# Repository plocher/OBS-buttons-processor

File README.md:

# OBS-buttons
## License: CERN Open Hardware Licence v1.2

Processor Board for Arduino Keyboard Box

An Arduino Pro-mini and connectors for IO daughterboard

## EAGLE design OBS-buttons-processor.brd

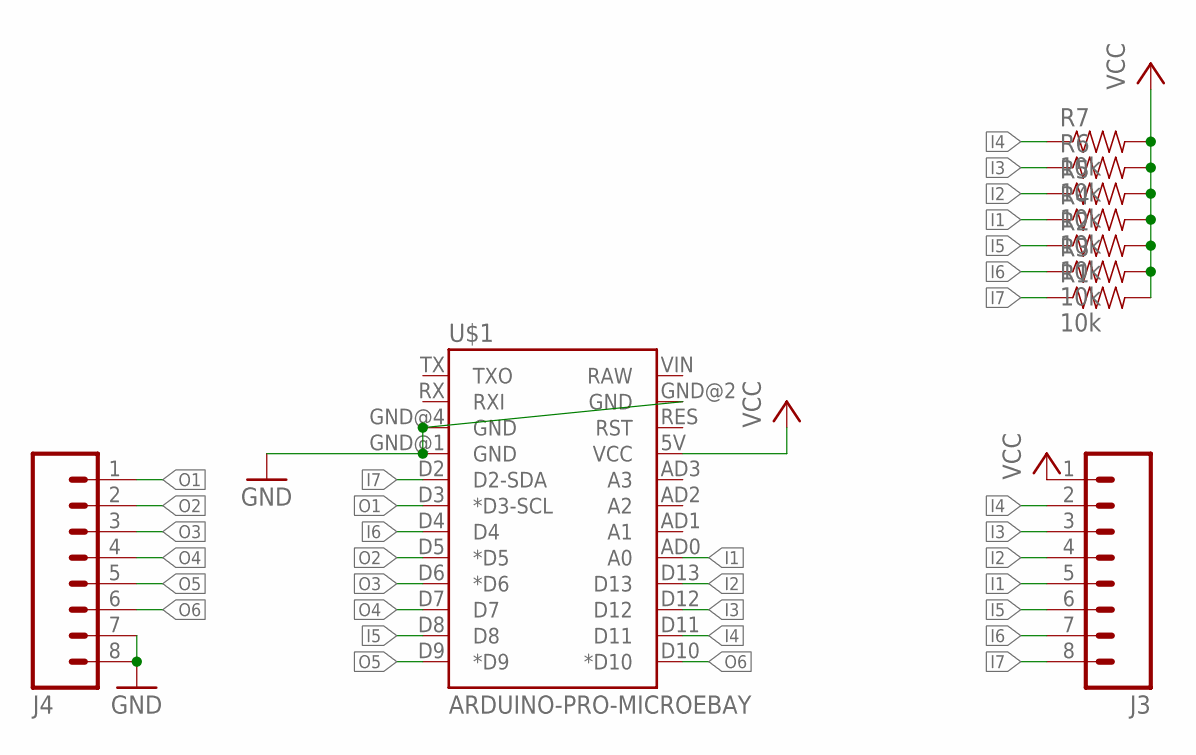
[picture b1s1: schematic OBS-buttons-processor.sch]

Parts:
J3, J4: CONNECTOR-M08LOCK; 1X08_LOCK
R1, R2, R3, R4, R5, R6, R7: 10k; AXIAL-0.4-RES
U$1: ARDUINO-PRO-MICROEBAY; ARDUINO-PRO-MICRO

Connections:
GND: J4.7, J4.8, U$1.GND@1 (GND), U$1.GND@2 (GND), U$1.GND@4 (GND)
I1: J3.5, R4.P$1 (1), U$1.AD0 (A0)
I2: J3.4, R5.P$1 (1), U$1.D13
I3: J3.3, R6.P$1 (1), U$1.D12
I4: J3.2, R7.P$1 (1), U$1.D11
I5: J3.6, R2.P$1 (1), U$1.D8
I6: J3.7, R3.P$1 (1), U$1.D4
I7: J3.8, R1.P$1 (1), U$1.D2 (D2-SDA)
O1: J4.1, U$1.D3 (*D3-SCL)
O2: J4.2, U$1.D5 (*D5)
O3: J4.3, U$1.D6 (*D6)
O4: J4.4, U$1.D7
O5: J4.5, U$1.D9 (*D9)
O6: J4.6, U$1.D10 (*D10)
VCC: J3.1, R1.P$2 (2), R2.P$2 (2), R3.P$2 (2), R4.P$2 (2), R5.P$2 (2), R6.P$2 (2), R7.P$2 (2), U$1.5V (VCC)

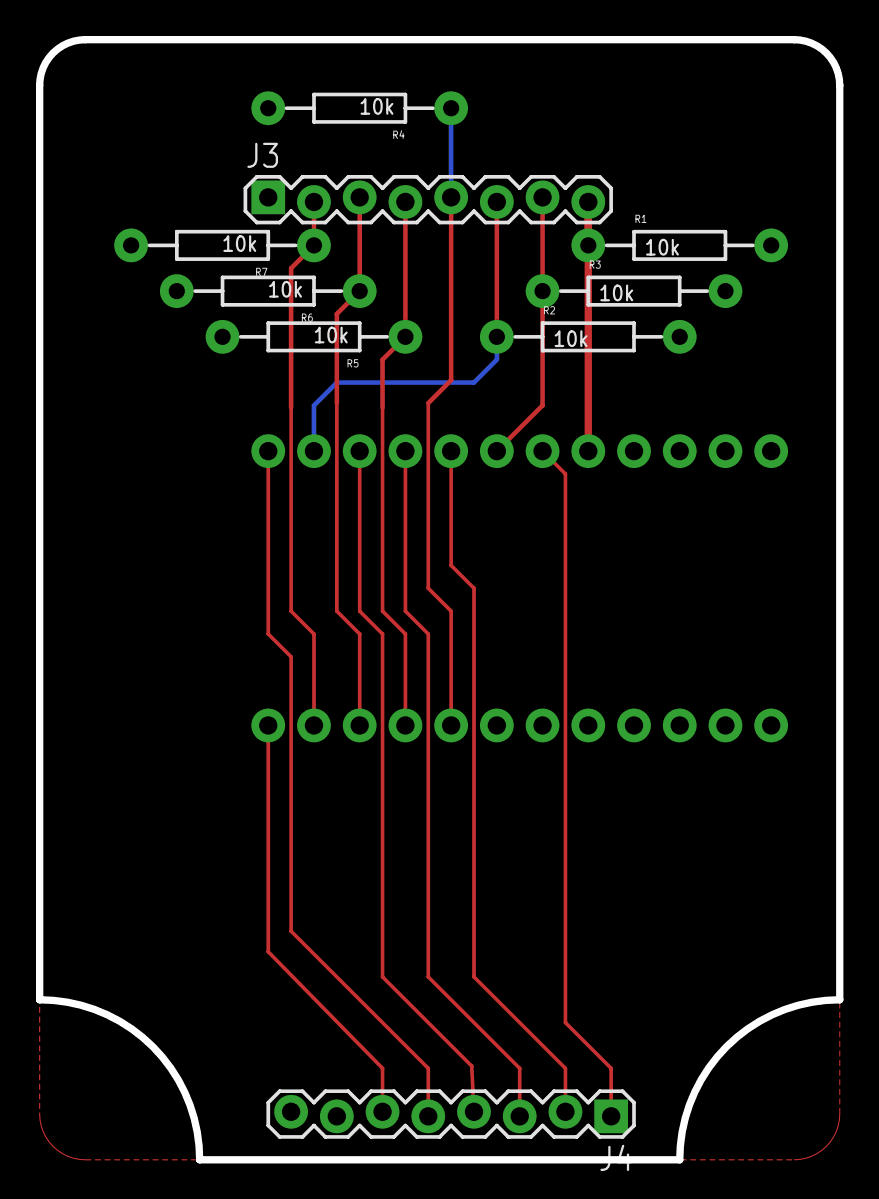
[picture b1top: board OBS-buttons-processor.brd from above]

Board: 2 copper layers, 44.5 x 62.2 mm, 10 parts (0 on the bottom side), 15 nets.

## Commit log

2020-11-14 Initial version
2020-11-18 initial prototype
